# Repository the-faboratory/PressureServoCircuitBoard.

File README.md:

# Pneumatic Regulator git repository
This repository contains (hopefully) everything needed to replicate the pneumatic regulator presented in

J. W. Booth, J. C. Case, E. L. White, D. S. Shah, and R. Kramer-Bottiglio, “[An addressable pneumatic regulator for distributed control of soft robots](10.1109/ROBOSOFT.2018.8404892),” in 2018 IEEE International Conference on Soft Robotics (RoboSoft).

It will be called "pneumatic regulator" and "pressure regulator" interchangeably.

If you have comments, suggestions, or want additional information, including how to obtain a pre-programmed and pre-assembled pressure regulator, please contact Joran Booth at JoranBooth@gmail.com. Being a research lab affiliated with a non-profit university, we are unable to sell regulators through our Yale affiliations. However, we are exploring commercializing the boards out of a small garage operation, depending on interest levels and applicable laws.

## Getting Started

### Prerequisites

Download MPLAB IDE(http://www.microchip.com/mplab/mplab-x-ide), with the XC compilers.

A detailed programming guide, with notes on the PressureRegulator's state machine, is in repository_guide.docx.

There are two versions of the hardware, with different connectors: one with 0.1" headers, and one with a MOLEX connector.

### Installing / Using
Programming a device is as easy as 1,2,3,...4:
```
1. Open the PIC_I2C.X project in MPLAB.
2. Change the variable I2C_ADDRESS to contain 2x the address you want the Arduino to call your PIC. Example: Arduino talks to sensor at address 8. I2C_ADDRESS = 2x8 = 16
3. Click "clean and build" to make sure it is compiling properly for your computer. (If you get a compiler error, try opening project properties and use C standard 90 (Project properties -> XC8 Global Options -> C Standard))
4. Click "Make and Program Device Main Project", to download the program to your PIC using a PicIt3 (the 'red box').
```

## Testing The Firmware

For your first test, use the Arduino driver pneumatic_regulator_driver.ino, or the sample Arduino Wire library code. For your I2C pullup, use 3.3k or 4.7k.

## Explanation of files (see each file for details):

File/Directory |  Purpose |
----- | --------- |
arduino_driver | Folder containing sample Arduino driver for communicating with the pressure regulators
auxiliary_files | Additional documentation, and a Microchip I2C application note.
pcb_files | Eagle files, bill of materials, and gerber files (for PCB.ng) for both versions of the regulator: 0.1" headers, and MOLEX connector
Pic_I2C.X | Project folder for programming the pneumatic regulator's PIC microcontroller using MPLAB.
PicIt3_user_guide | [A guide to using the PICkit3](http://ww1.microchip.com/downloads/en/DeviceDoc/50002010B.pdf). Made by Microchip.
pressure_regulator_i2c.c | Firmware for the pressure regulator's PIC microcontroller, to control pressure manually or use Bang-Bang with a deadband to regulate the pressure at the output (i.e., in your actuator).
repository_guide.docx | An explanation of how to download firmware to a PIC, using this repository.

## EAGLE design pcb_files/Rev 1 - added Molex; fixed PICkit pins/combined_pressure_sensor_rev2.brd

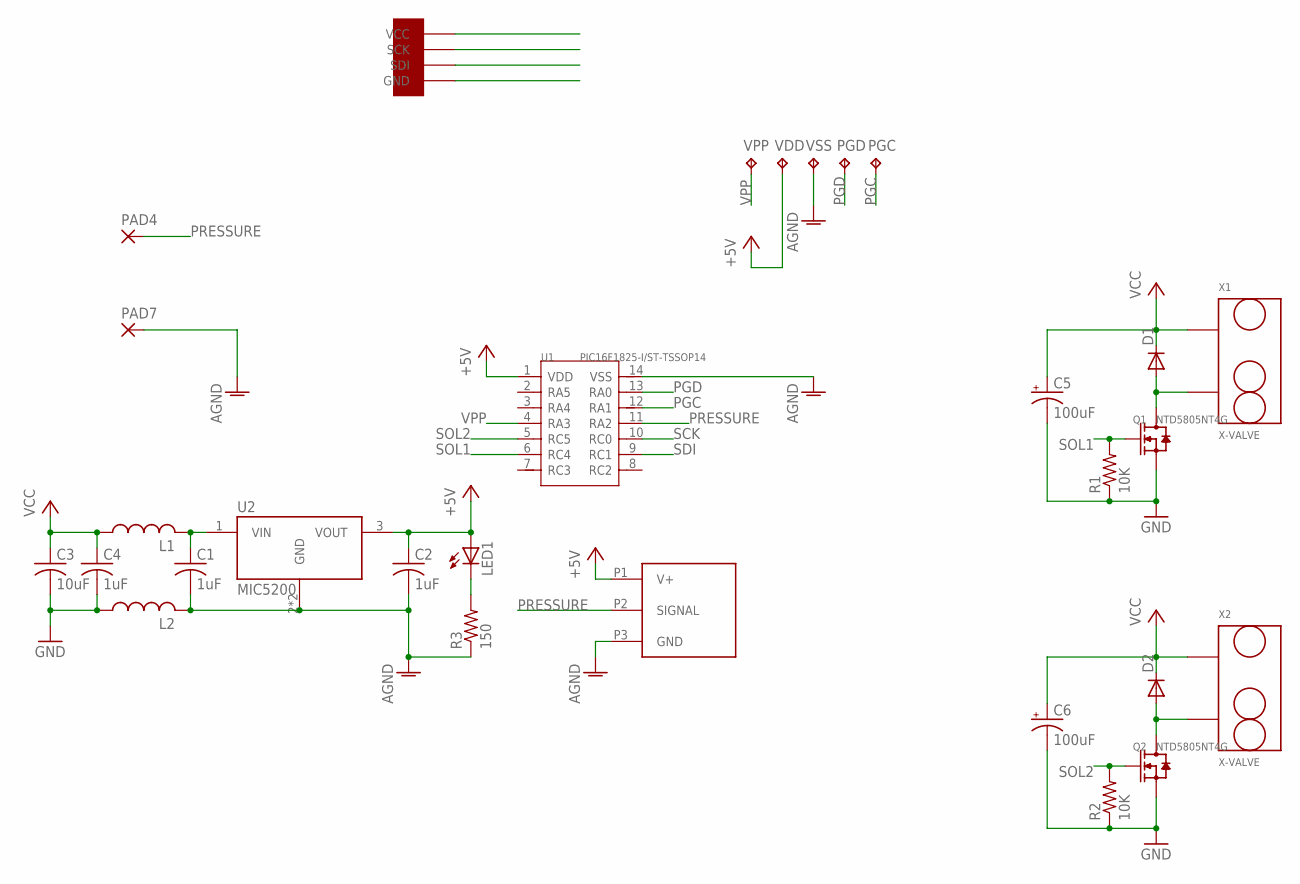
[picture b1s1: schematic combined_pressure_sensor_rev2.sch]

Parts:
C1, C2, C4: 1uF; C0603
C3: 10uF; C1206
C5, C6: 100uF; 153CLV-0605
D1, D2: DIODE-SOD523; SOD523
L1, L2: L-USL1206; L1206
LED1: LEDCHIP-LED0603; CHIP-LED0603
PAD4, PAD7: SMD2; SMD1,27-2,54
PGC: TPB1,27; B1,27
PGD: TPB1,27; B1,27
Q1, Q2: NTD5805NT4G; DPAK
R1, R2: 10K; R0603
R3: 150; R0603
U1: PIC16F1825-I/ST-TSSOP14; TSSOP14-0.65-5X4.4MM
U2: MIC5200; SOT223
U$1: PICOBLADE4POS1.25MMRIGHTANGLESURFACE; PICOBLADE4POSMALEHEADER
U$3: ASDX
VDD: TPB1,27; B1,27
VPP: TPB1,27; B1,27
VSS: TPB1,27; B1,27
X1, X2: X-VALVE

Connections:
+5V: C2.1, LED1.A, U1.1 (VDD), U2.3 (VOUT), U$3.P1 (V+), VDD.TP
AGND: C1.2, C2.2, L2.2, PAD7.1, R3.1, U1.14 (VSS), U2.2 (GND), U2.4 (GND), U$3.P3 (GND), VSS.TP
GND: C3.2, C4.2, C5.-, C6.-, L2.1, Q1.2 (S), Q2.2 (S), R1.1, R2.1, U$1.GND
unnamed: D1.A, Q1.3 (D), X1.P$2
unnamed: D2.A, Q2.3 (D), X2.P$2
unnamed: C1.1, L1.2, U2.1 (VIN)
unnamed: LED1.C, R3.2
PGC: PGC.TP, U1.12 (RA1)
PGD: PGD.TP, U1.13 (RA0)
PRESSURE: PAD4.1, U1.11 (RA2), U$3.P2 (SIGNAL)
SCK: U1.10 (RC0), U$1.SCK
SDI: U1.9 (RC1), U$1.SDI
SOL1: Q1.1 (G), R1.2, U1.6 (RC4)
SOL2: Q2.1 (G), R2.2, U1.5 (RC5)
VCC: C3.1, C4.1, C5.+, C6.+, D1.C, D2.C, L1.1, U$1.VCC, X1.P$1, X2.P$1
VPP: U1.4 (RA3), VPP.TP

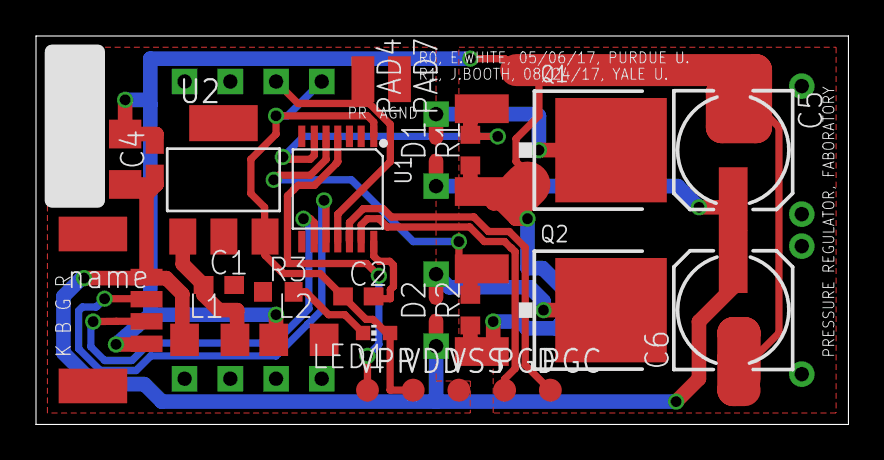
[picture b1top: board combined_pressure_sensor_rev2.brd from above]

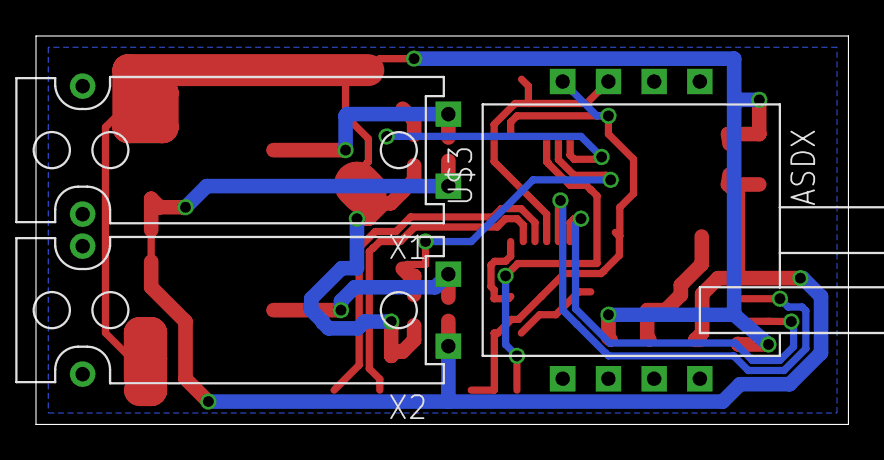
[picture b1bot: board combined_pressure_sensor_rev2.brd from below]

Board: 2 copper layers, 45.1 x 21.6 mm, 29 parts (3 on the bottom side), 16 nets.

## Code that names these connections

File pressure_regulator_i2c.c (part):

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#pragma config FOSC = INTOSC    // INTOSC oscillator: I/O function on CLKIN pin
#pragma config WDTE = ON        // Watchdog Timer Enable (WDT enabled) Dyl off
#pragma config PWRTE = ON       // Power-up Timer Enable (PWRT enabled) Dyl Off
#pragma config MCLRE = ON       // MCLR/VPP pin function is MCLR
#pragma config CP = ON          // Program memory code protection is enabled Dyl Off
#pragma config CPD = ON         // Data memory code protection is enabled Dyl off
#pragma config BOREN = ON       // Brown-out Reset enabled
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

// Global algorithm variables
#define INDEX_SETPOINT_HIGH_BYTE    16 // High byte of our desired actuator set point.  Default setpoint is atmospheric pressure (2.5V -> HighByte = 127 = -0.147 PSI)
#define INDEX_SETPOINT_LOW_BYTE 17 // Low byte of our desired actuator power
#define INDEX_DESIRED_STATE    18 // State. 0 = Release, 1 = Hold, 2 = Inflate. Our desired state. This is only active during manual mode.  Default valve state is hold (both valves off).
#define INDEX_PRESSURE_SENSOR_HIGH_BYTE 19 // High byte of our actuator's pressure sensor
#define INDEX_PRESSURE_SENSOR_LOW_BYTE 20  // Low byte of our actuator's pressure sensor
#define INDEX_HALF_BAND 21 // 1/2*How wide our bang-bang deadband should be. Default Half-band is 10 [ADC values] = 2.94 [PSI]
#define INDEX_OPERATION_MODE 22 // What mode should we operate in? automatic = 0. manual = 1.  Default mode is manual
#define INDEX_ONLY_SEND_PRESSURE 23 // If == 0, then the i2cArray can be read. ElseIf == 1, every read results in reading pressure. Default read mode is "only send pressure"
#define Nop() {_asm nop _endasm} // Dyl define the NOP function for doing nothing https://www.microchip.com/forums/m156162.aspx
#define _XTAL_FREQ 32000000 // internal oscillator: 32 MHz
unsigned int setPointHigh;       // high byte of the setpoint
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    // initialize: Configures the clock, ADC, I/O, I2C module, and Initialize variables
    
    // Use comparitor 1
    // Capacitor voltage on C1IN+ (Pin 13) RA0
    // Vdd/3 on C12IN0- (Pin 12) RA1 Dylan VDD/21
    // 2Vdd/3 on C12IN2- (Pin 8) RC2 Dylan VDD*11/21
    // Capacitor charge (Pin 6) RC4
    // Charging indicator on (Pin 5) RC5

    // Filter measurement on AN2 (Pin 11) RA2

    // SPI Port:
    // SCK on (Pin 10) RC0
    // SDI on (Pin 9) RC1
    // SDO on (Pin 3) RA4 [APFCON0]
    // SS1 on (Pin 7) RC3 [APFCON0]
    // I2C Port: SDA (Pin 9) RC1 / SCL (Pin 10) RC0 Dyl


    // uC setup
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    GIE = 1; // Enable global interrupts

    // ADC Configuration
    TRISAbits.TRISA2 = 1; // RA2 set as input p 120
    ANSELAbits.ANSA2 = 1;
    ADCON0bits.ADON = 1; // enable the ADC module
    ADCON1 = 0b01100000; // left justified, Fosc/64, Vss, Vdd
    
    
    // MOSFET Configurations
    TRISCbits.TRISC4 = 0; // RC4
    LATCbits.LATC4 = 0;
    TRISCbits.TRISC5 = 0; // RC5
    LATCbits.LATC5 = 0;
    
    // Initialize values in i2cArray
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
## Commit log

2018-02-20 Add files via upload
    These are the base files for the pressure regulator.
2018-02-20 Add files via upload
    Adds the arduino files for connecting to the servo.
2020-05-09 Clean up, add c firmware, add .gitignore, add bill of materials and gerber files
2020-05-09 minor readme updates
